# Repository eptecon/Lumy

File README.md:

Lumy: Smart Connected LED Lighting System
======

Lumy is a smart connected LED lighting system comprising multiple interconnectable modules.

### Hardware

Lumy hardware comprises following modules:

- LumyCtrl: power supply, main microcontroller (ATMega328P) interface to WiFi module and interface to LED driver
- LumyDrv: 4x TI LM3404 LED driver with 1.2A output each
- LumyLight: LED carrier board, can be populated with up to 12 Cree high power LEDs arranged in 3 separate strings with up to 4 LEDs each
- LumySense: ambient light sensor TSL2591  

### Firmware

Lumy firmware is a simple bare metal C program running on the ATMega328P. It controls the brightness of connected LEDs over PWM inputs of the LED drivers
depending on sensor or user input. The user input is provided over a simple android app, which sends the data wirelessly over WiFi to the Lumy system.

---

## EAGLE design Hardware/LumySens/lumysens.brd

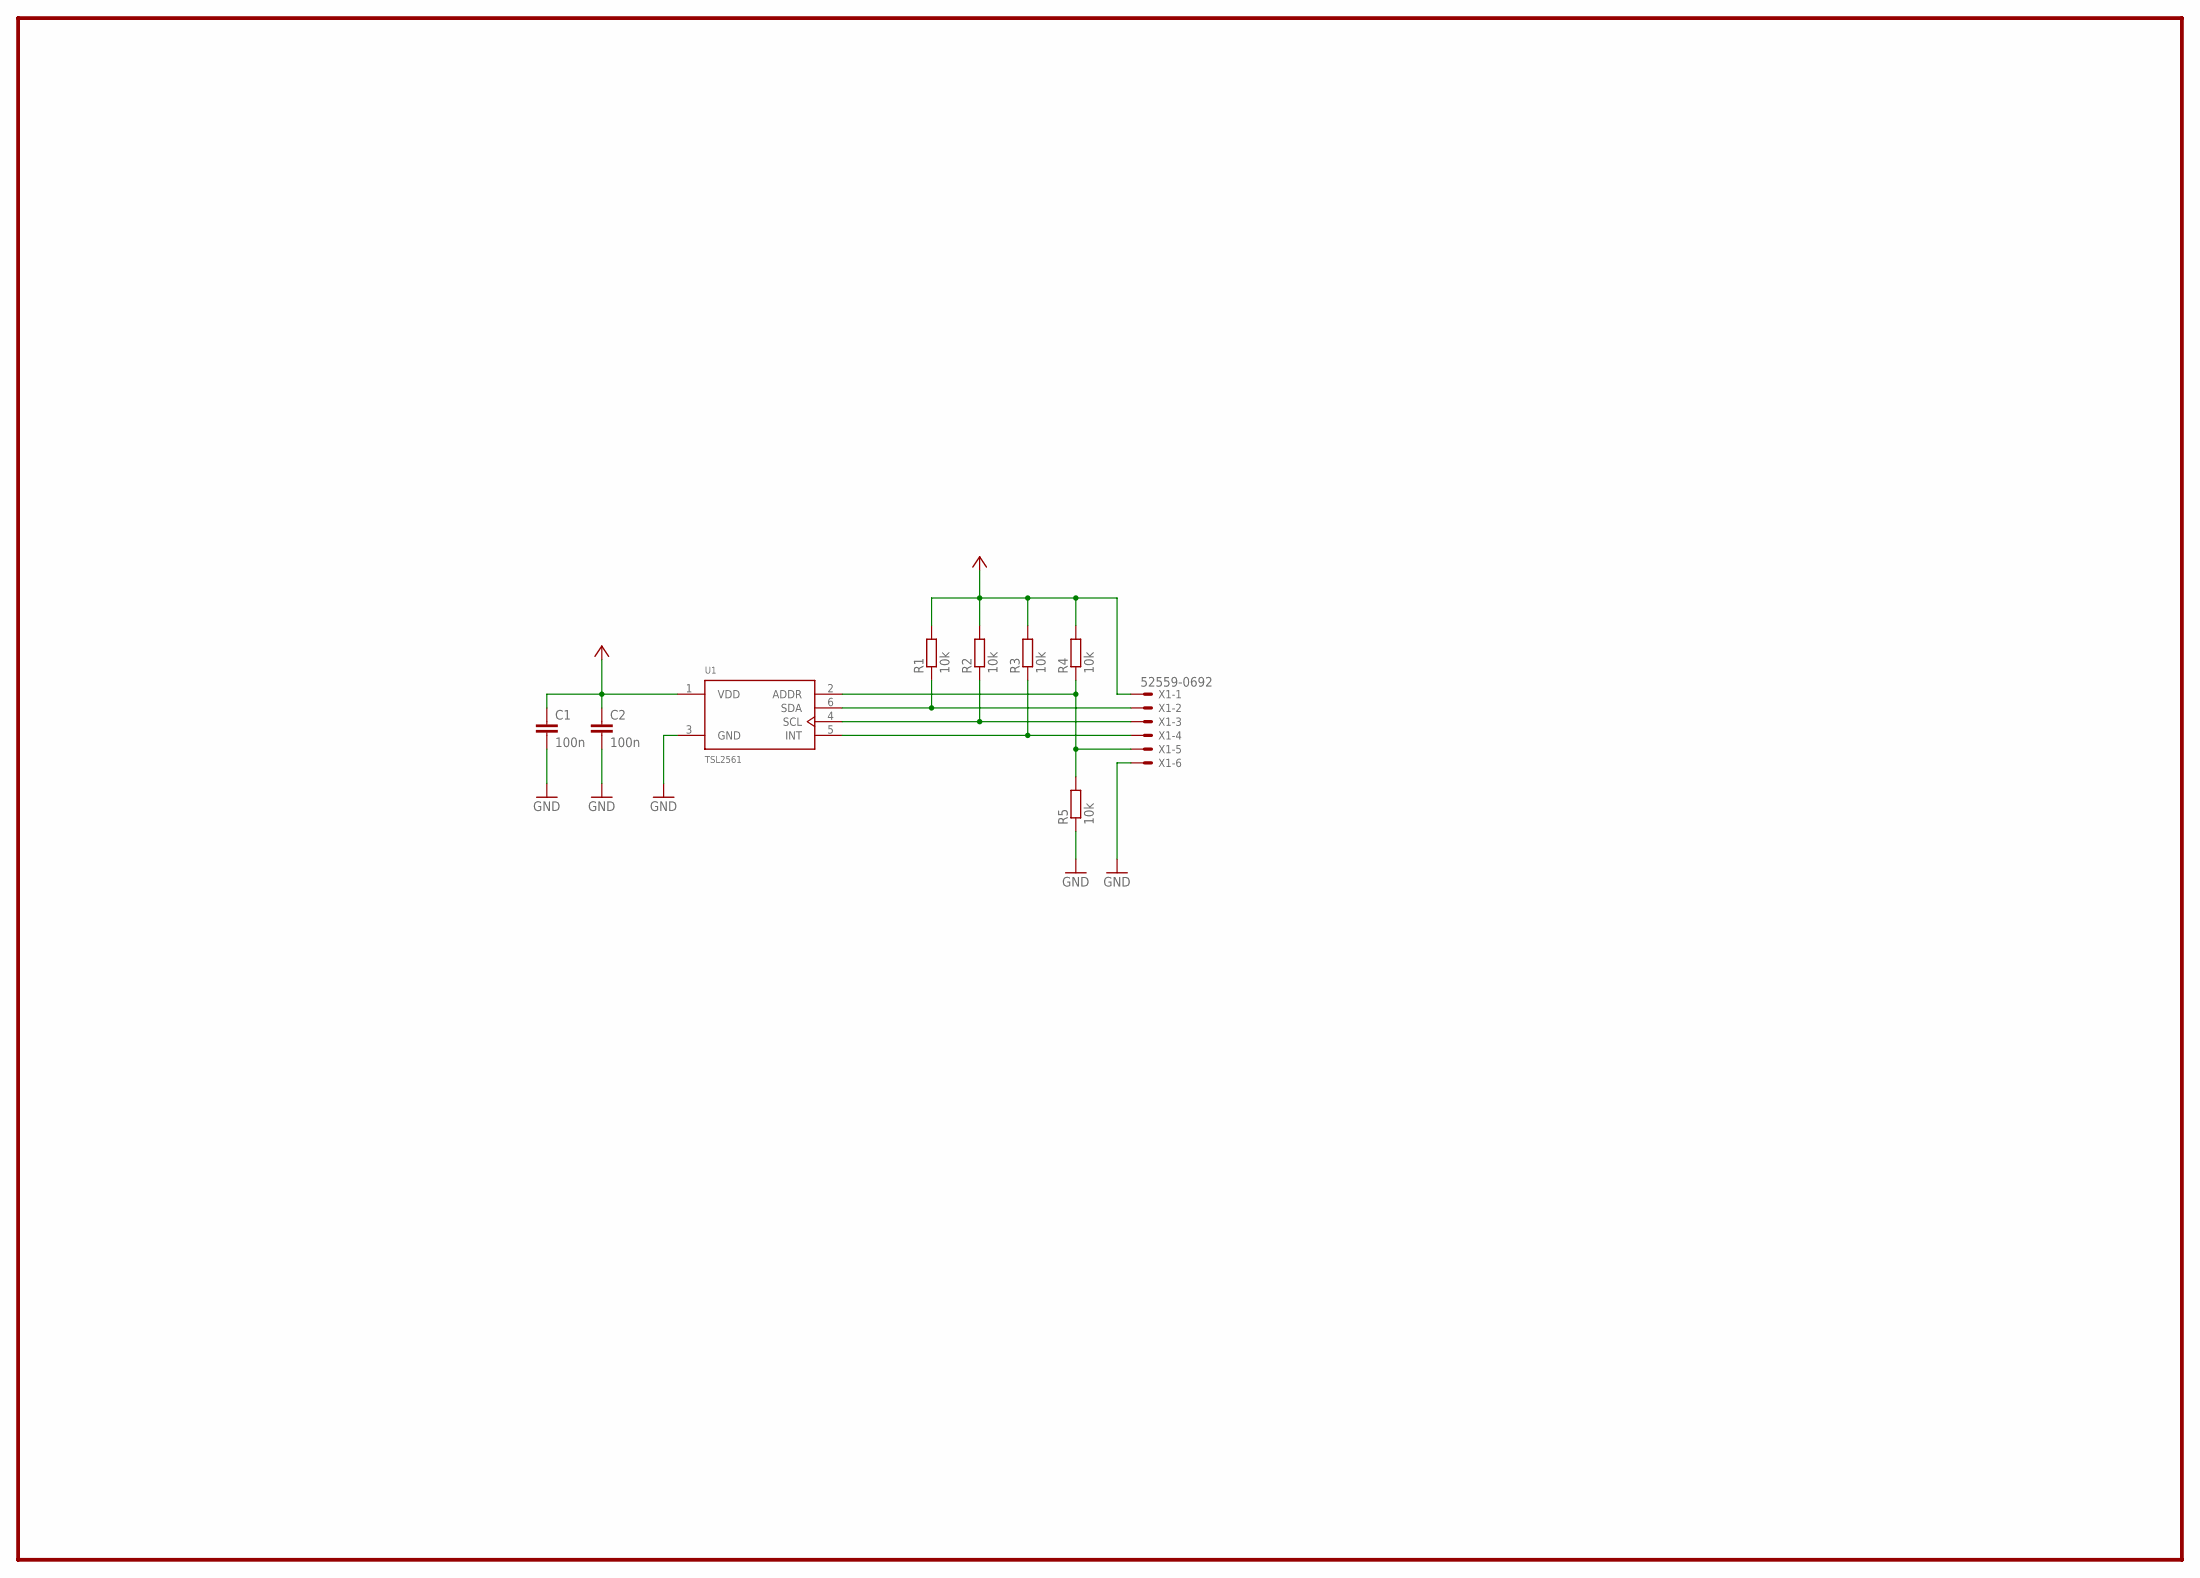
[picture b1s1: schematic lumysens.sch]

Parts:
C1, C2: 100n; C0603
R1, R2, R3, R4, R5: 10k; R0603
U1: TSL2561; TMB-6
X1: 52559-0692

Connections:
+3V3: C1.1, C2.1, R1.2, R2.2, R3.2, R4.2, U1.1 (VDD), X1.1
GND: C1.2, C2.2, R5.1, U1.3 (GND), X1.6
unnamed: R4.1, R5.2, U1.2 (ADDR), X1.5
unnamed: R1.1, U1.6 (SDA), X1.2
unnamed: R2.1, U1.4 (SCL), X1.3
unnamed: R3.1, U1.5 (INT), X1.4

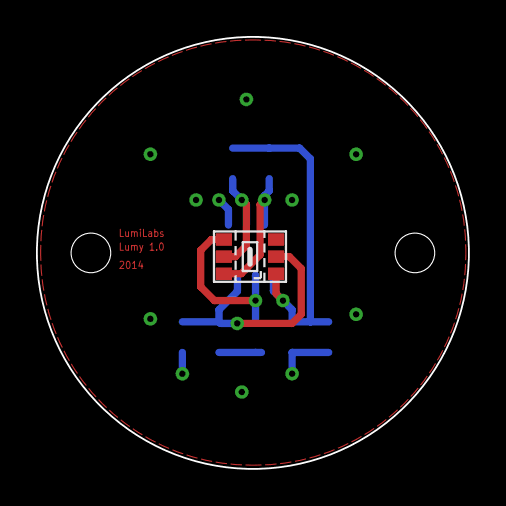
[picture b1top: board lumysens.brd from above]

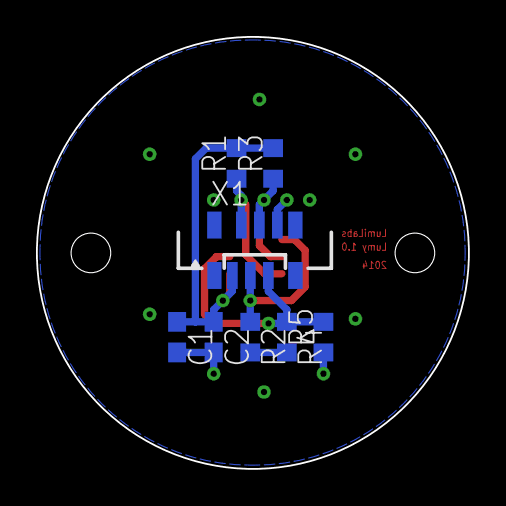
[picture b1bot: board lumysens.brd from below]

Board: 2 copper layers, 24.0 x 24.0 mm, 9 parts (8 on the bottom side), 6 nets.

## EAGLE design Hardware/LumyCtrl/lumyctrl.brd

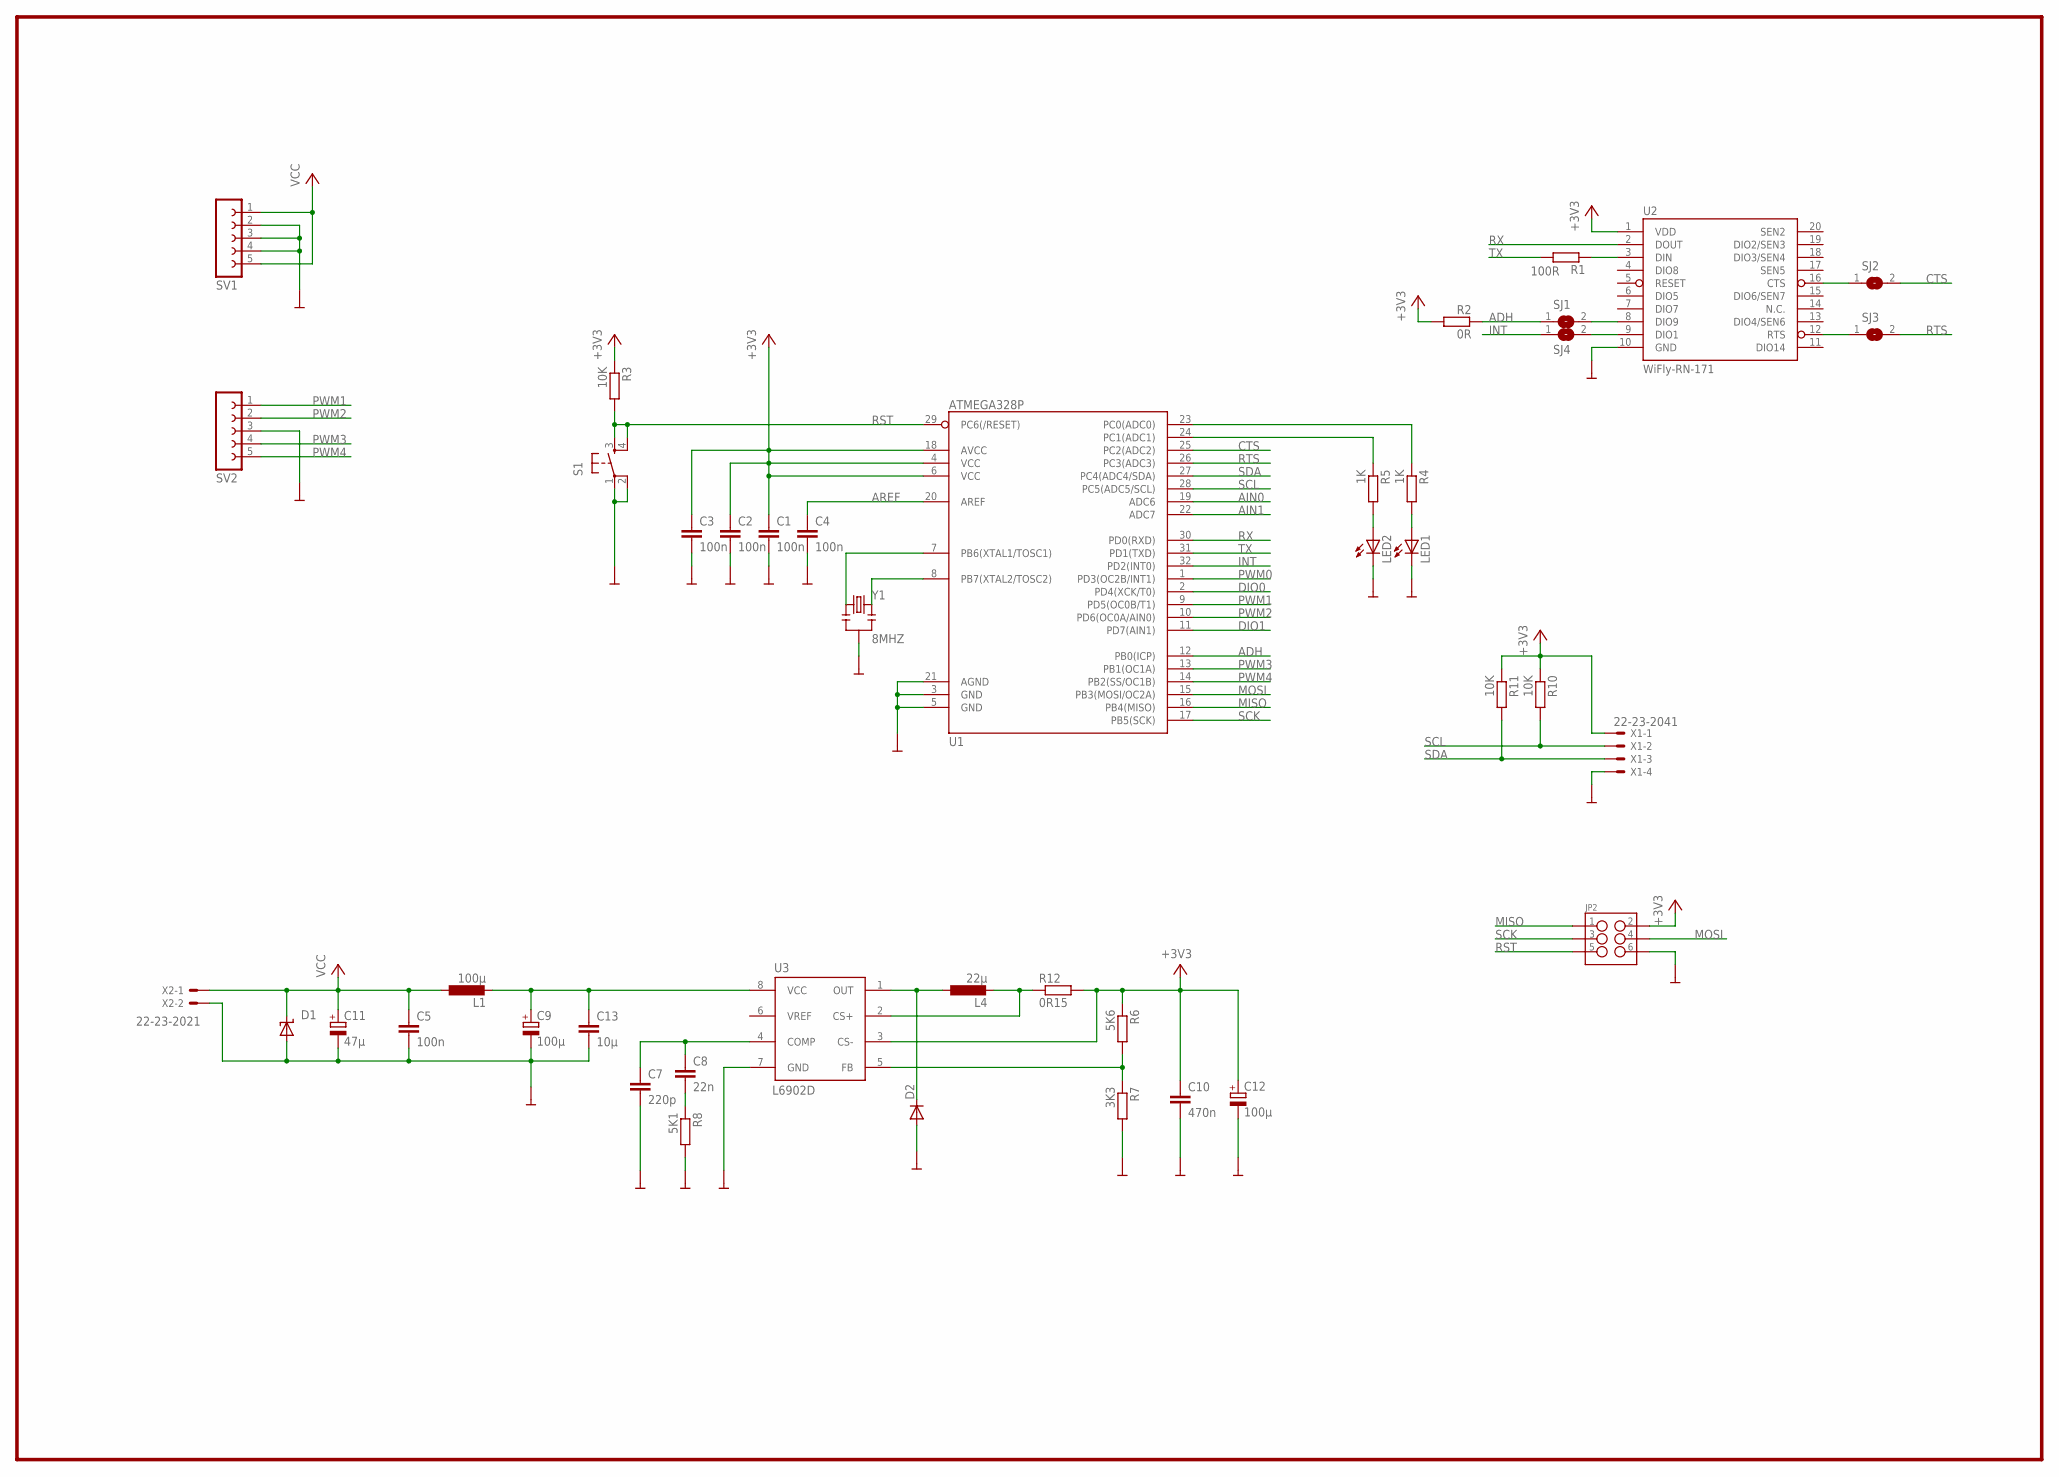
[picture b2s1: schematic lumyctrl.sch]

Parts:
C1, C2, C3, C4, C5: 100n; C0603
C7: 220p; C0603
C8: 22n; C0603
C9, C12: 100µ; SMC_C
C10: 470n; C0603
C11: 47µ; SMC_E
C13: 10µ; C1206
D1: SUPPRESSOR-SMBJ; SMBJ
D2: DIODESMA; SMA-DIODE
JP2: M03X2SMT; 2X3_SMT_POSTS
L1: 100µ; POWER-CHOKE_WE-TPC
L4: 22µ; POWER-CHOKE_WE-TPC
LED1, LED2: LEDCHIP-LED0603; CHIP-LED0603
R1: 100R; R0603
R2: 0R; R0603
R3, R10, R11: 10K; R0603
R4, R5: 1K; R0603
R6: 5K6; R0603
R7: 3K3; R0603
R8: 5K1; R0603
R12: 0R15; R2512
S1: TAC_SWITCHSMD; TACTILE_SWITCH_SMD
SJ1, SJ2, SJ3, SJ4: SJ
SV1, SV2: FE05-1
U1: ATMEGA328P; TQFP32-08
U2: WiFly-RN-171; XBEE-SMD
U3: L6902D; SO08
X1: 22-23-2041
X2: 22-23-2021
Y1: 8MHZ; RESONATOR-SMD

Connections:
+3V3: C1.1, C2.1, C3.1, C10.1, C12.+, JP2.2, R2.2, R3.1, R6.1, R10.1, R11.1, R12.2, U1.4 (VCC), U1.6 (VCC), U1.18 (AVCC), U2.1 (VDD), U3.3 (CS-), X1.1
ADH: R2.1, SJ1.1, U1.12 (PB0(ICP))
AIN0: U1.19 (ADC6)
AIN1: U1.22 (ADC7)
AREF: C4.1, U1.20 (AREF)
CTS: SJ2.2, U1.25 (PC2(ADC2))
DIO0: U1.2 (PD4(XCK/T0))
DIO1: U1.11 (PD7(AIN1))
GND: C1.2, C2.2, C3.2, C4.2, C5.2, C7.2, C9.-, C10.2, C11.-, C12.-, C13.2, D1.A, D2.A, JP2.6, LED1.C, LED2.C, R7.2, R8.2, S1.1, S1.2, SV1.2, SV1.3, SV1.4, SV2.3, U1.3 (GND), U1.5 (GND), U1.21 (AGND), U2.10 (GND), U3.7 (GND), X1.4, X2.2, Y1.2
INT: SJ4.1, U1.32 (PD2(INT0))
MISO: JP2.1, U1.16 (PB4(MISO))
MOSI: JP2.4, U1.15 (PB3(MOSI/OC2A))
unnamed: R1.1, U2.3 (DIN)
unnamed: SJ1.2, U2.8 (DIO9)
unnamed: D2.C, L4.1, U3.1 (OUT)
unnamed: U1.7 (PB6(XTAL1/TOSC1)), Y1.1
unnamed: U1.8 (PB7(XTAL2/TOSC2)), Y1.3
unnamed: SJ3.1, U2.12 (RTS)
unnamed: SJ2.1, U2.16 (CTS)
unnamed: R6.2, R7.1, U3.5 (FB)
unnamed: C9.+, C13.1, L1.2, U3.8 (VCC)
unnamed: C7.1, C8.1, U3.4 (COMP)
unnamed: LED2.A, R5.2
unnamed: C8.2, R8.1
unnamed: LED1.A, R4.2
unnamed: R4.1, U1.23 (PC0(ADC0))
unnamed: R5.1, U1.24 (PC1(ADC1))
unnamed: L4.2, R12.1, U3.2 (CS+)
unnamed: SJ4.2, U2.9 (DIO1)
PWM0: U1.1 (PD3(OC2B/INT1))
PWM1: SV2.1, U1.9 (PD5(OC0B/T1))
PWM2: SV2.2, U1.10 (PD6(OC0A/AIN0))
PWM3: SV2.4, U1.13 (PB1(OC1A))
PWM4: SV2.5, U1.14 (PB2(SS/OC1B))
RST: JP2.5, R3.2, S1.3, S1.4, U1.29 (PC6(/RESET))
RTS: SJ3.2, U1.26 (PC3(ADC3))
RX: U1.30 (PD0(RXD)), U2.2 (DOUT)
SCK: JP2.3, U1.17 (PB5(SCK))
SCL: R10.2, U1.28 (PC5(ADC5/SCL)), X1.2
SDA: R11.2, U1.27 (PC4(ADC4/SDA)), X1.3
TX: R1.2, U1.31 (PD1(TXD))
VCC: C5.1, C11.+, D1.C, L1.1, SV1.1, SV1.5, X2.1

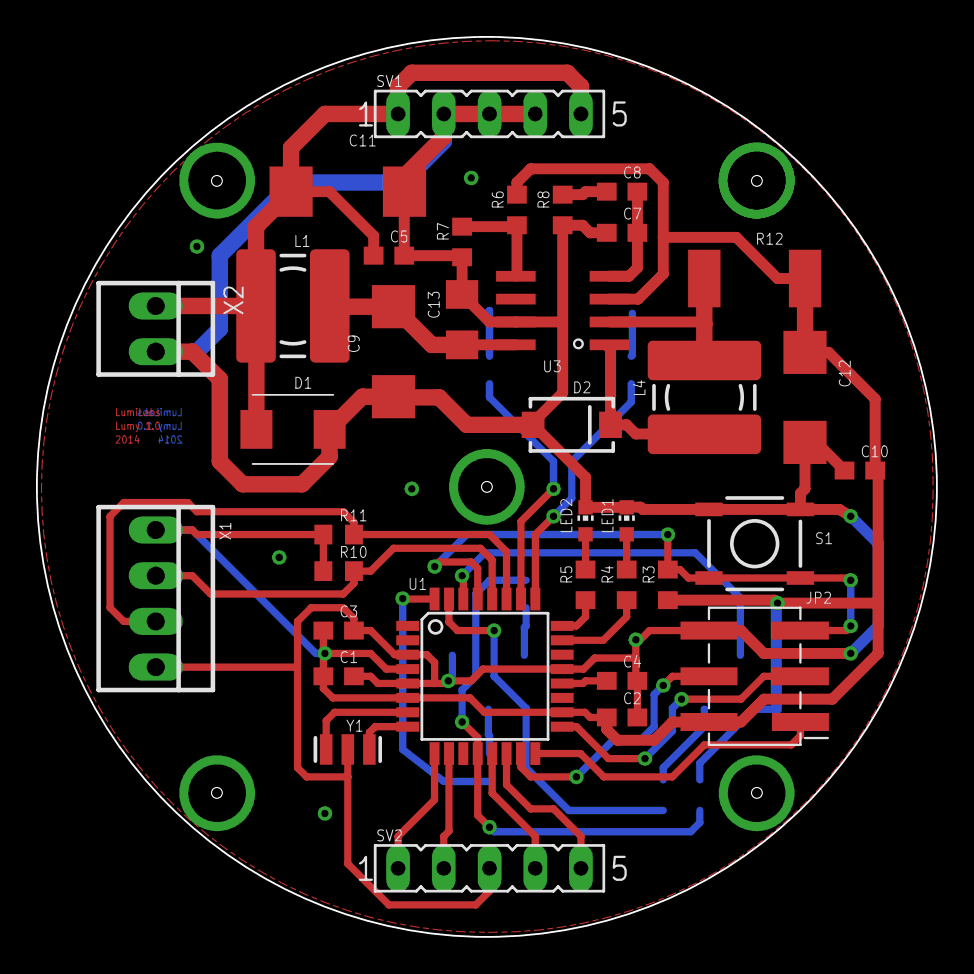
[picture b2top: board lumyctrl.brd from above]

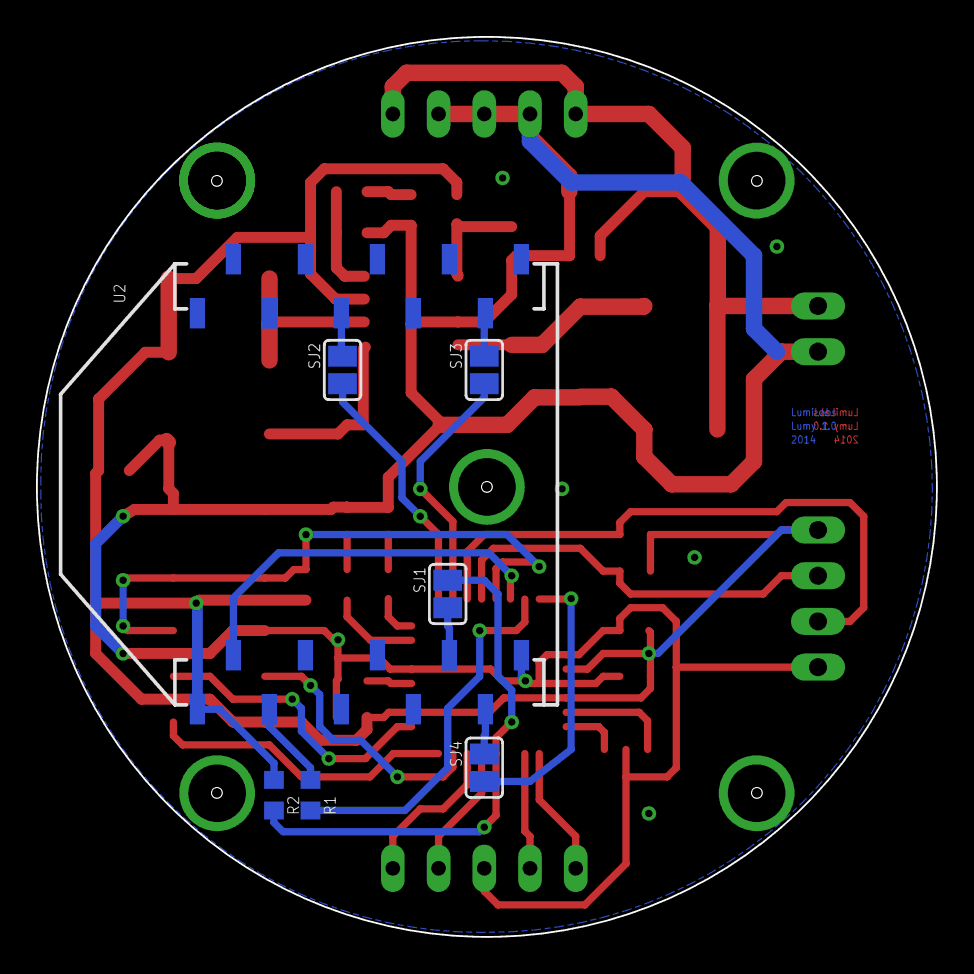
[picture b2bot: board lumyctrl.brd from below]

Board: 2 copper layers, 50.0 x 50.0 mm, 43 parts (7 on the bottom side), 37 nets.

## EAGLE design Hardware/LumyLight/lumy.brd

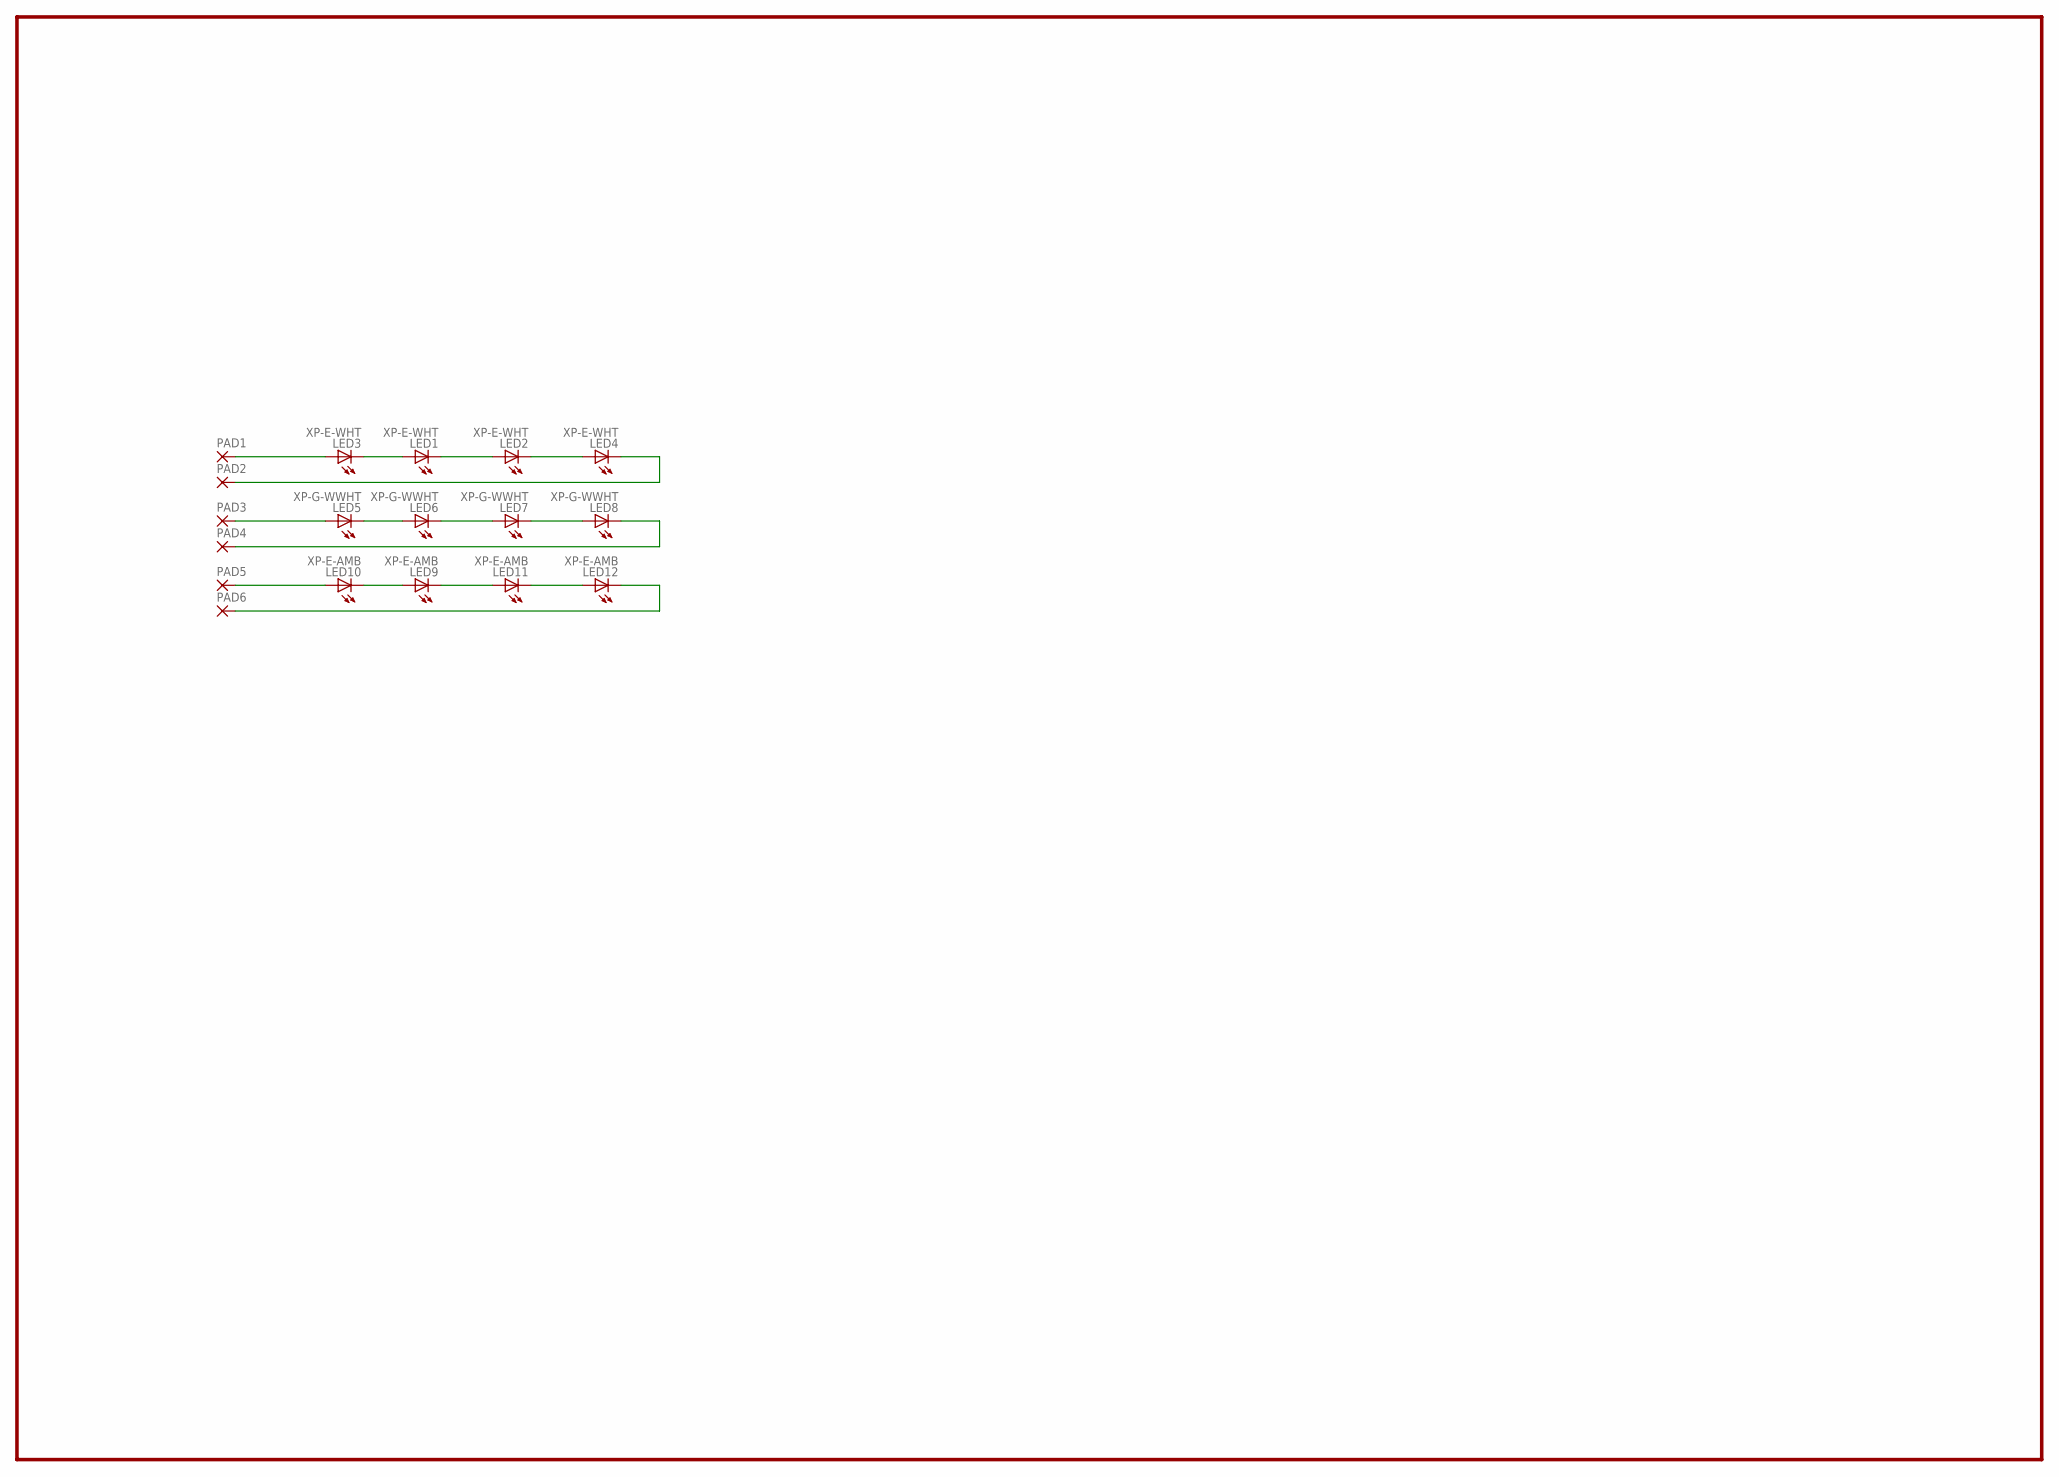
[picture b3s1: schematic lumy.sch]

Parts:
LED1, LED2, LED3, LED4: XP-E-WHT; CREE_XLAMP
LED5, LED6, LED7, LED8: XP-G-WWHT; CREE_XLAMP
LED9, LED10, LED11, LED12: XP-E-AMB; CREE_XLAMP
PAD1, PAD2, PAD3, PAD4, PAD5, PAD6: SMD2; SMD1,27-2,54

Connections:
unnamed: LED1.A, LED1.A@1 (A), LED3.C, LED3.C@1 (C)
unnamed: LED1.C, LED1.C@1 (C), LED2.A, LED2.A@1 (A)
unnamed: LED2.C, LED2.C@1 (C), LED4.A, LED4.A@1 (A)
unnamed: LED7.C, LED7.C@1 (C), LED8.A, LED8.A@1 (A)
unnamed: LED6.C, LED6.C@1 (C), LED7.A, LED7.A@1 (A)
unnamed: LED5.C, LED5.C@1 (C), LED6.A, LED6.A@1 (A)
unnamed: LED3.A, LED3.A@1 (A), PAD1.1
unnamed: LED9.A, LED9.A@1 (A), LED10.C, LED10.C@1 (C)
unnamed: LED9.C, LED9.C@1 (C), LED11.A, LED11.A@1 (A)
unnamed: LED11.C, LED11.C@1 (C), LED12.A, LED12.A@1 (A)
unnamed: LED4.C, LED4.C@1 (C), PAD2.1
unnamed: LED5.A, LED5.A@1 (A), PAD3.1
unnamed: LED8.C, LED8.C@1 (C), PAD4.1
unnamed: LED10.A, LED10.A@1 (A), PAD5.1
unnamed: LED12.C, LED12.C@1 (C), PAD6.1

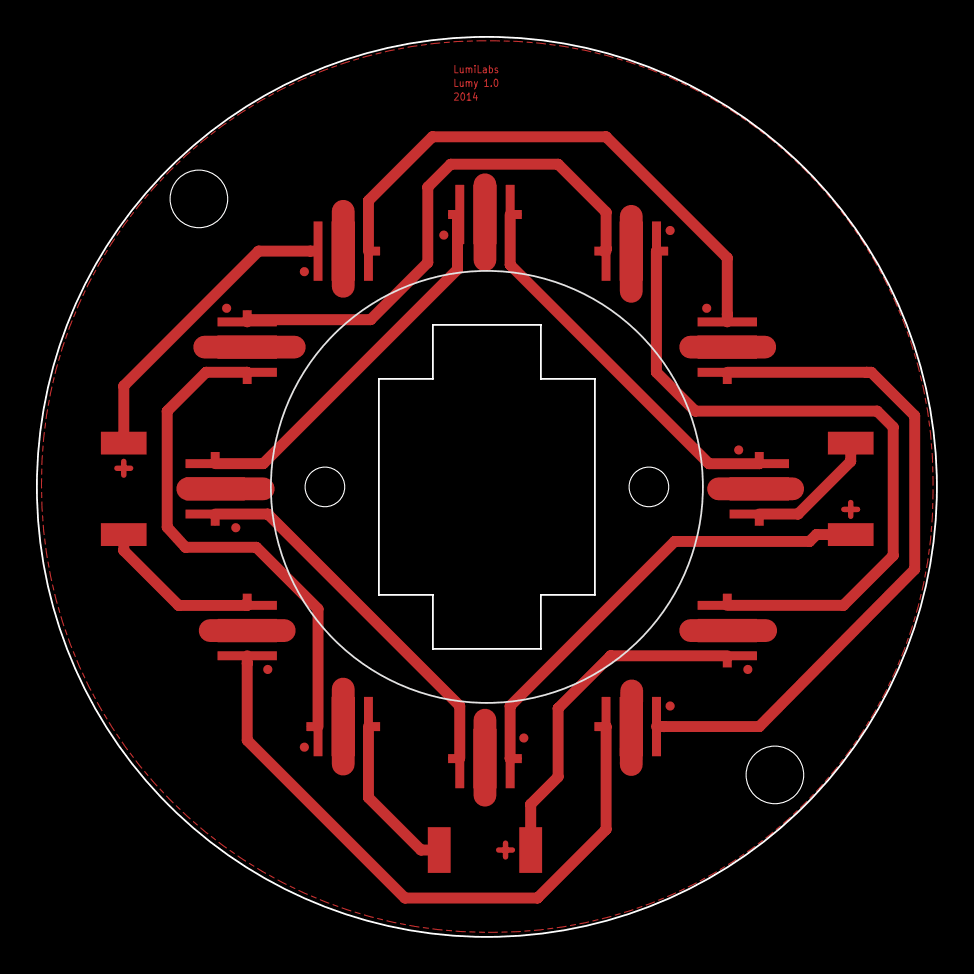
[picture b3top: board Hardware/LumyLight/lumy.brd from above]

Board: 2 copper layers, 50.0 x 50.0 mm, 18 parts (0 on the bottom side), 15 nets.

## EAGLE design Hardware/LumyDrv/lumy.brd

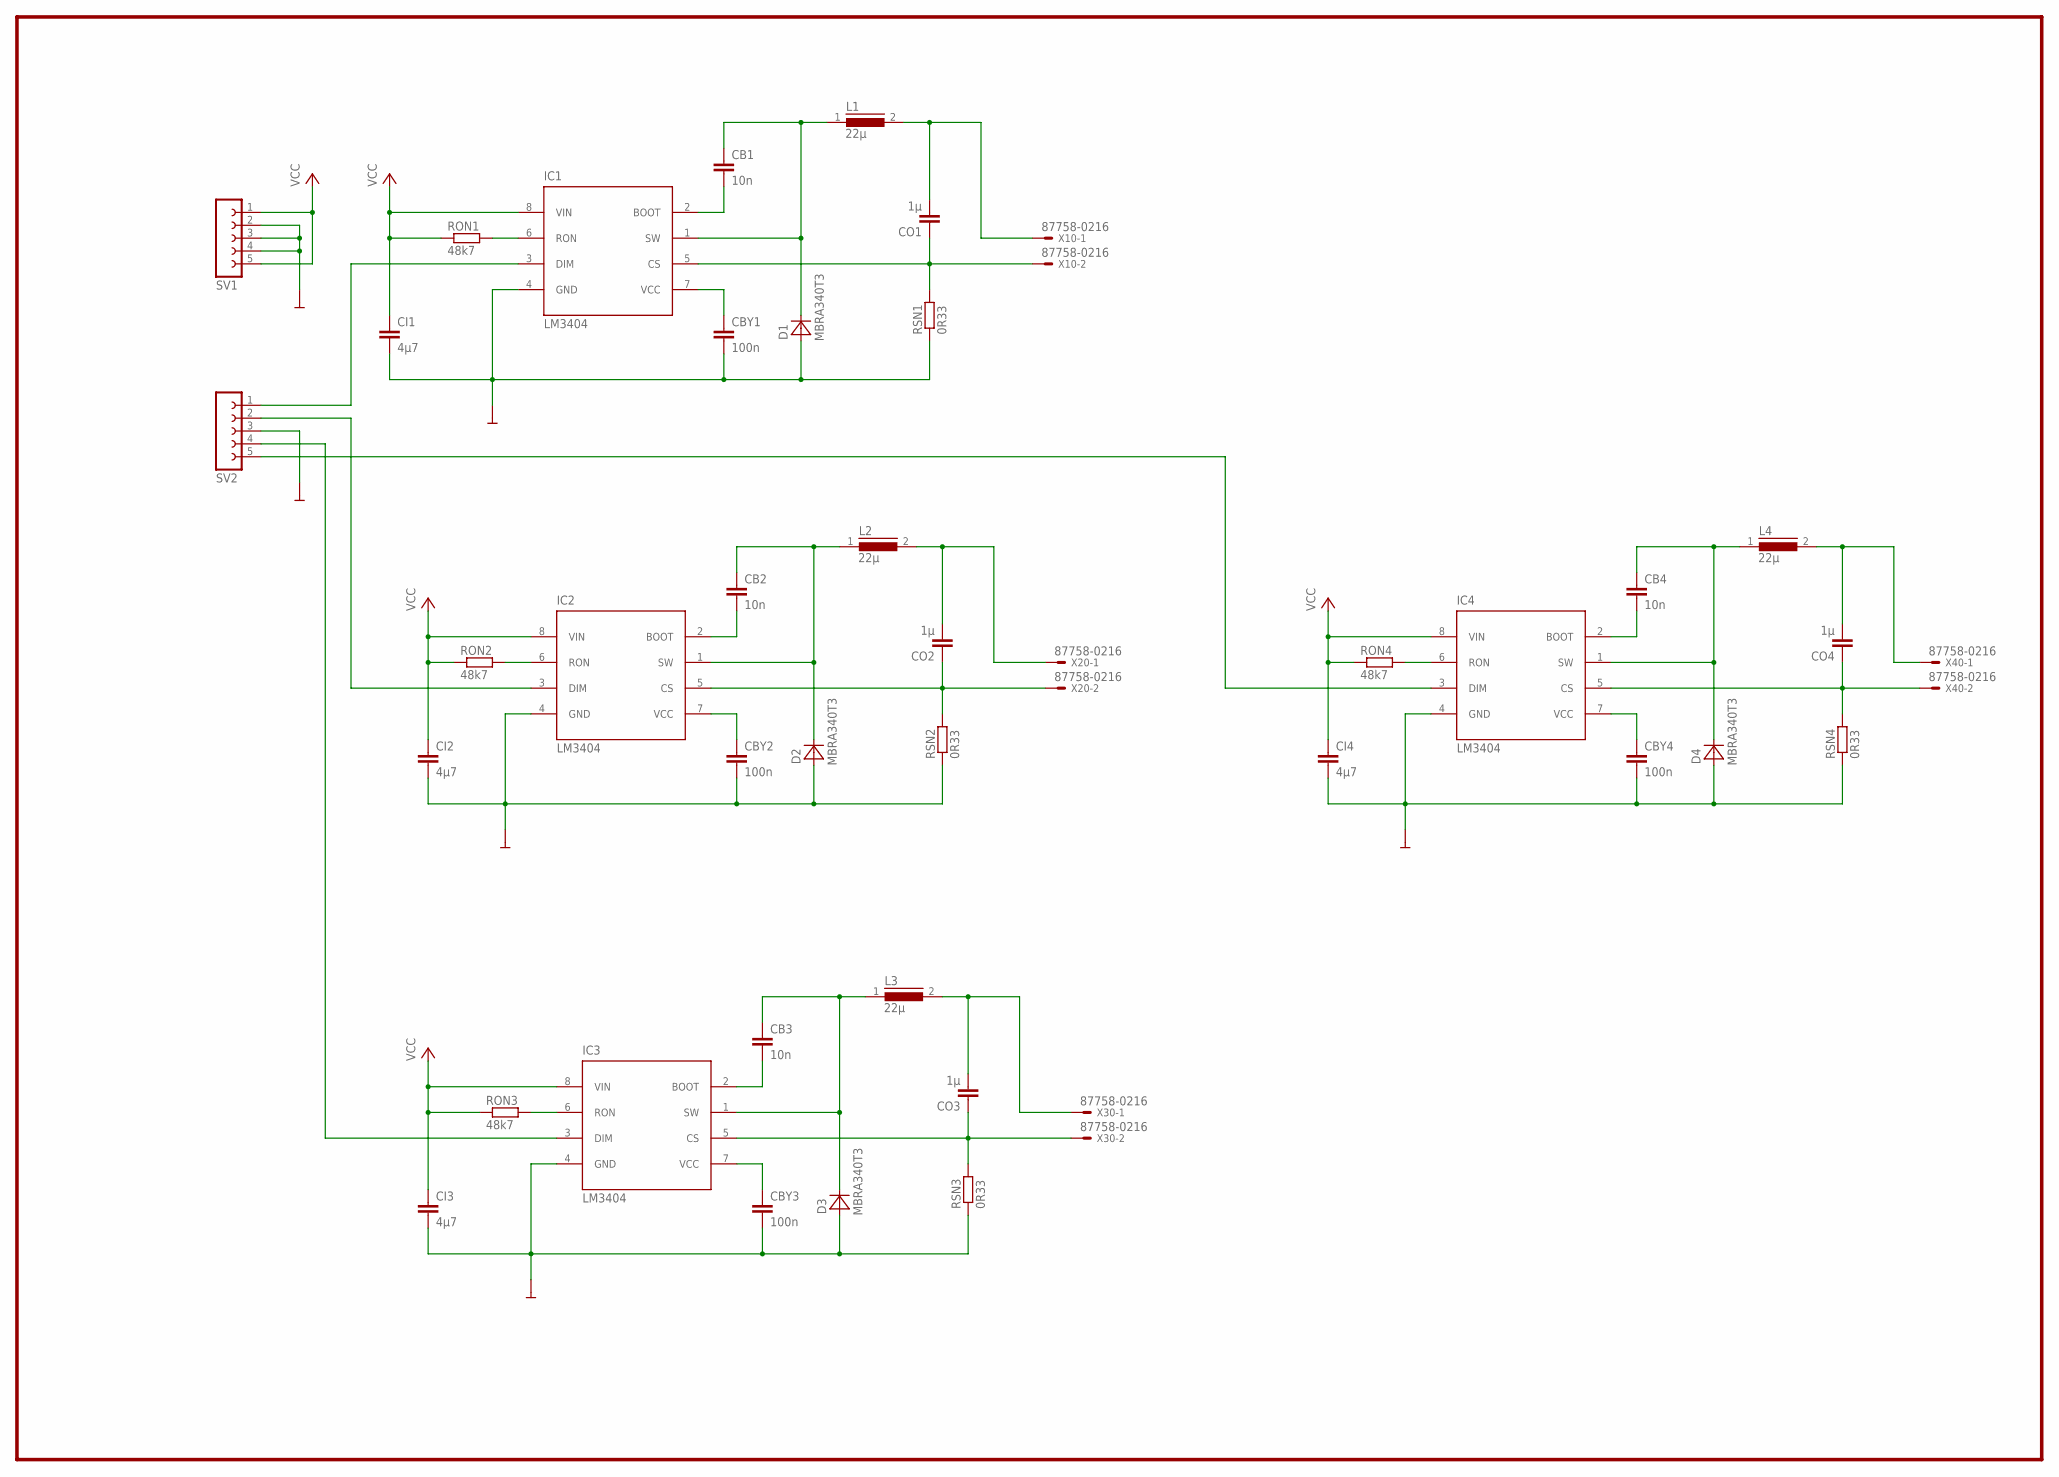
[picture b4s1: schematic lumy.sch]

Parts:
CB1, CB2, CB3, CB4: 10n; C0603
CBY1, CBY2, CBY3, CBY4: 100n; C0603
CI1, CI2, CI3, CI4: 4µ7; C0603
CO1, CO2, CO3, CO4: 1µ; C1206
D1, D2, D3, D4: MBRA340T3; SMA
IC1, IC2, IC3, IC4: LM3404; SO08
L1, L2, L3, L4: 22µ; DR73
RON1, RON2, RON3, RON4: 48k7; R0805
RSN1, RSN2, RSN3, RSN4: 0R33; R1206
SV1, SV2: FE05-1
X10, X20, X30: 87758-0216
X40: 87758-0216; MPN 87758-0216

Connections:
GND: CBY1.2, CBY2.2, CBY3.2, CBY4.2, CI1.2, CI2.2, CI3.2, CI4.2, D1.A, D2.A, D3.A, D4.A, IC1.4 (GND), IC2.4 (GND), IC3.4 (GND), IC4.4 (GND), RSN1.1, RSN2.1, RSN3.1, RSN4.1, SV1.2, SV1.3, SV1.4, SV2.3
unnamed: IC1.6 (RON), RON1.2
unnamed: CB1.1, D1.C, IC1.1 (SW), L1.1
unnamed: CBY1.1, IC1.7 (VCC)
unnamed: CO1.1, IC1.5 (CS), RSN1.2, X10.2
unnamed: CO1.2, L1.2, X10.1
unnamed: CB1.2, IC1.2 (BOOT)
unnamed: IC1.3 (DIM), SV2.1
unnamed: IC2.6 (RON), RON2.2
unnamed: CBY2.1, IC2.7 (VCC)
unnamed: CO2.1, IC2.5 (CS), RSN2.2, X20.2
unnamed: CO2.2, L2.2, X20.1
unnamed: CB2.1, D2.C, IC2.1 (SW), L2.1
unnamed: CB2.2, IC2.2 (BOOT)
unnamed: IC2.3 (DIM), SV2.2
unnamed: IC3.6 (RON), RON3.2
unnamed: CBY3.1, IC3.7 (VCC)
unnamed: CO3.1, IC3.5 (CS), RSN3.2, X30.2
unnamed: CO3.2, L3.2, X30.1
unnamed: CB3.1, D3.C, IC3.1 (SW), L3.1
unnamed: CB3.2, IC3.2 (BOOT)
unnamed: IC3.3 (DIM), SV2.4
unnamed: CBY4.1, IC4.7 (VCC)
unnamed: CB4.2, IC4.2 (BOOT)
unnamed: IC4.6 (RON), RON4.2
unnamed: CB4.1, D4.C, IC4.1 (SW), L4.1
unnamed: CO4.2, L4.2, X40.1
unnamed: CO4.1, IC4.5 (CS), RSN4.2, X40.2
unnamed: IC4.3 (DIM), SV2.5
VCC: CI1.1, CI2.1, CI3.1, CI4.1, IC1.8 (VIN), IC2.8 (VIN), IC3.8 (VIN), IC4.8 (VIN), RON1.1, RON2.1, RON3.1, RON4.1, SV1.1, SV1.5

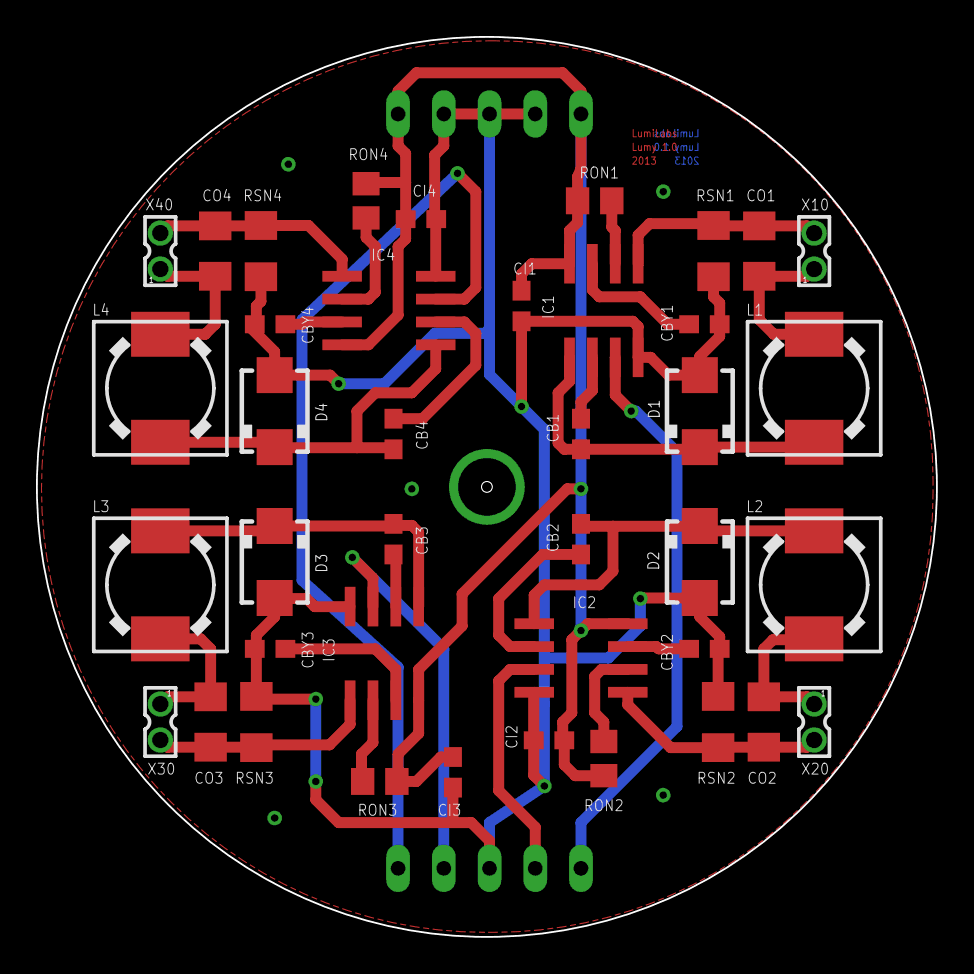
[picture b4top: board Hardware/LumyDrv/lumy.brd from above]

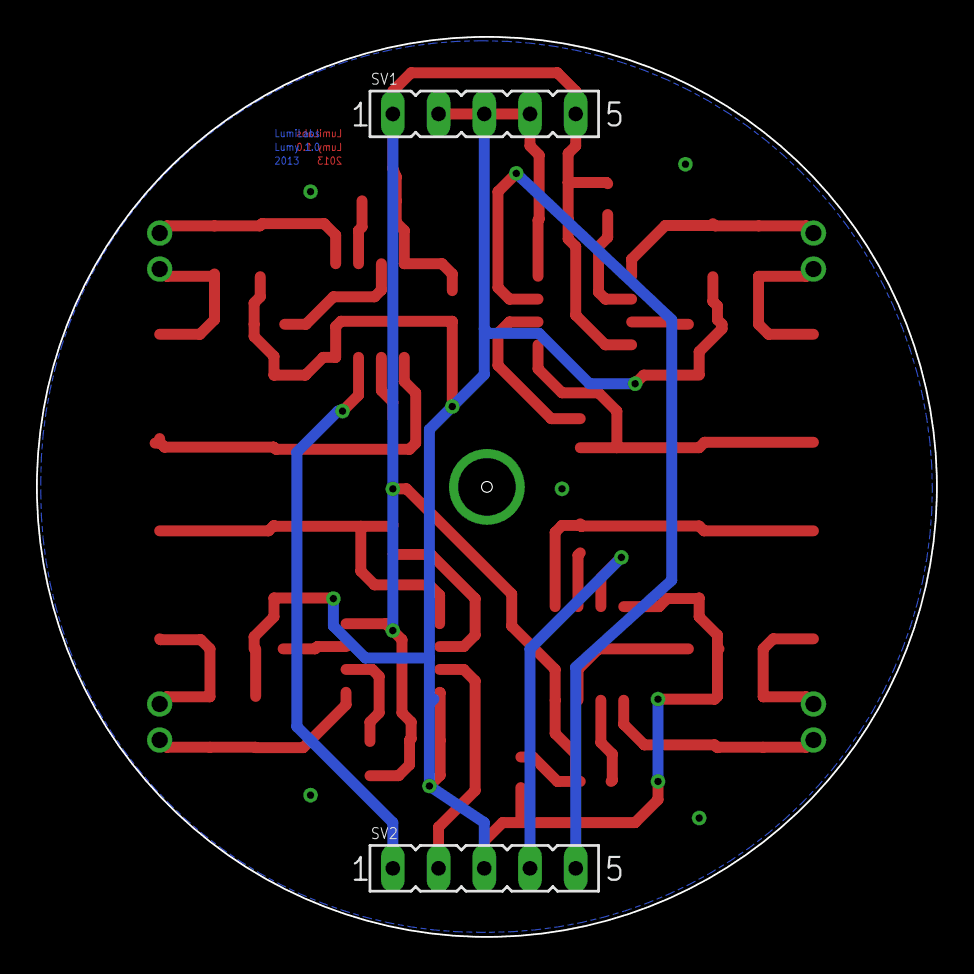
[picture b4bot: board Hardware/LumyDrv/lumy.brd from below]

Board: 2 copper layers, 50.0 x 50.0 mm, 42 parts (2 on the bottom side), 30 nets.

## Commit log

2021-05-28 readme updated
2021-05-28 readme updated 2
2021-05-28 added firmware code
2021-05-28 added firmware code readme, update makefile
2021-05-28 updated firmware code readme
2021-05-28 updated firmware code
2021-05-28 added LumySense
2021-06-28 readme and docu updated, license added
2021-06-28 readme and docu updated

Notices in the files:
parts and their libraries:
SparkFun-RF: Licensing: CC v3.0 Share-Alike You are welcome to use this library for commercial purposes.
eagle-library-edeca.net-v5: This is v1 and is licensed under the Creative Commons (Attribution-Non-Commercial-Share Alike 2.0 UK)
